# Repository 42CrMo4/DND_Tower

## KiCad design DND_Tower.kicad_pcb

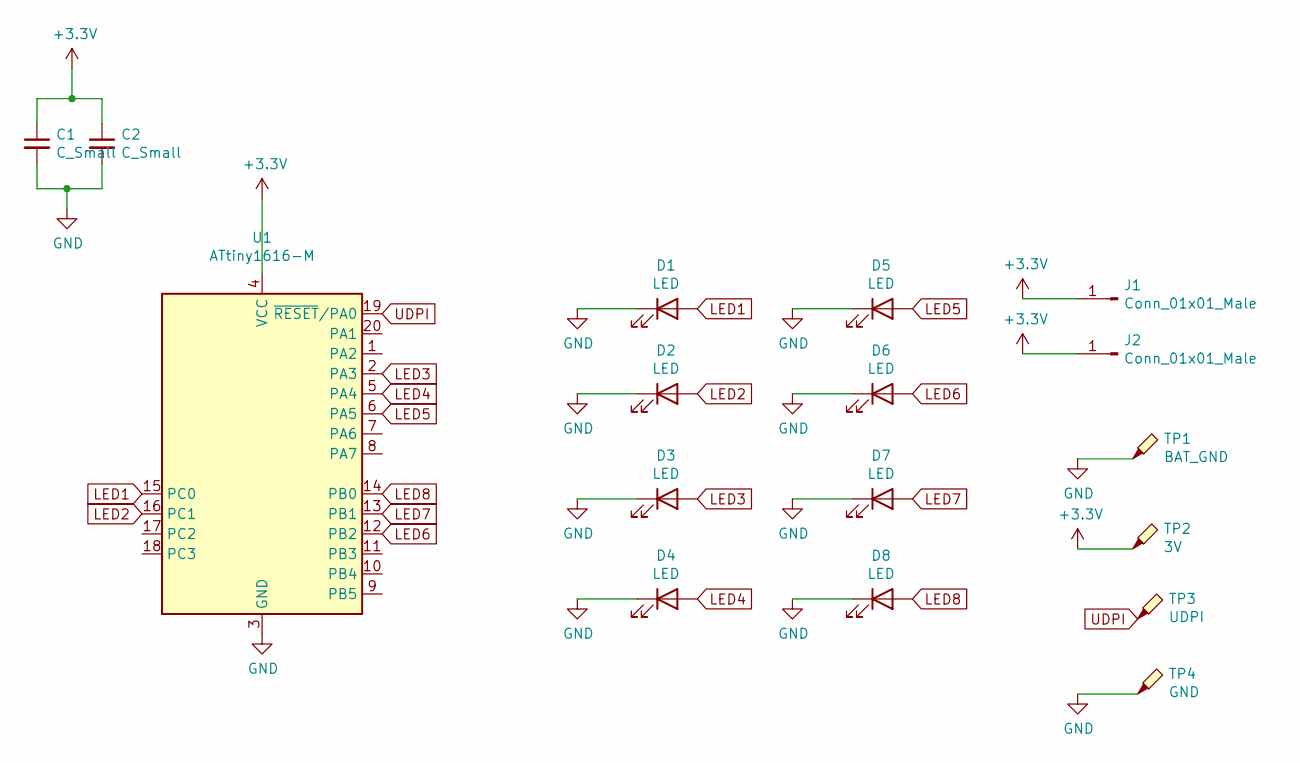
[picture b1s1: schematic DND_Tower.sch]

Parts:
C1, C2: C_Small; C_0805_2012Metric
D1, D2, D3, D4, D5, D6, D7, D8: LED; LED_0805_2012Metric
J1, J2: Conn_01x01_Male; Pin_D1.4mm_L8.5mm_W2.8mm_FlatFork
TP1: BAT_GND; TestPoint_Pad_D4.0mm
TP2: 3V; TestPoint_Pad_D1.0mm
TP3: UDPI; TestPoint_Pad_D1.0mm
TP4: GND; TestPoint_Pad_D1.0mm
U1: ATtiny1616-M; VQFN-20-1EP_3x3mm_P0.4mm_EP1.7x1.7mm

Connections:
+3V3: C1.1, C2.1, J1.1, J2.1, TP2.1, U1.4 (VCC)
GND: C1.2, C2.2, D1.1 (K), D2.1 (K), D3.1 (K), D4.1 (K), D5.1 (K), D6.1 (K), D7.1 (K), D8.1 (K), TP1.1, TP4.1, U1.3 (GND), U1.21 (GND)
LED1: D1.2 (A), U1.15 (PC0)
LED2: D2.2 (A), U1.16 (PC1)
LED3: D3.2 (A), U1.2 (PA3)
LED4: D4.2 (A), U1.5 (PA4)
LED5: D5.2 (A), U1.6 (PA5)
LED6: D6.2 (A), U1.12 (PB2)
LED7: D7.2 (A), U1.13 (PB1)
LED8: D8.2 (A), U1.14 (PB0)
UDPI: TP3.1, U1.19 (~RESET~/PA0)

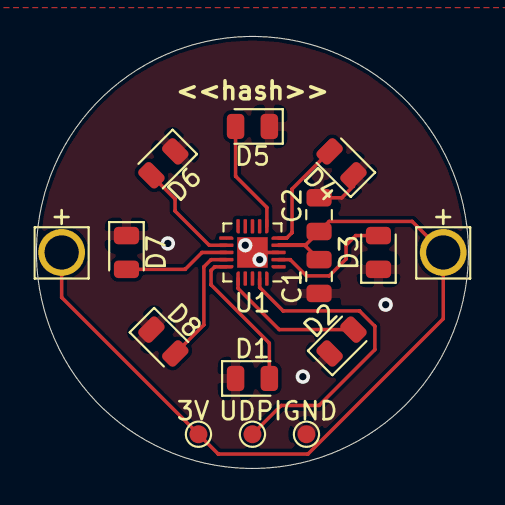
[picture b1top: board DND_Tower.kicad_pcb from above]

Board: 2 copper layers, 24.0 x 24.0 mm, 17 parts (1 on the bottom side), 11 nets.

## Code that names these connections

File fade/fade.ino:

/*
  Fade

  This example shows how to fade an LED on pin 9 using the analogWrite()
  function.

  The analogWrite() function uses PWM, so if you want to change the pin you're
  using, be sure to use another PWM capable pin. On most Arduino, the PWM pins
  are identified with a "~" sign, like ~3, ~5, ~6, ~9, ~10 and ~11.

  This example code is in the public domain.

  https://www.arduino.cc/en/Tutorial/BuiltInExamples/Fade
*/

int led1 = PIN_PC0;           // the PWM pin the LED is attached to
int led2 = PIN_PC1;           // the PWM pin the LED is attached to
int led3 = PIN_PA3;           // the PWM pin the LED is attached to
int led4 = PIN_PA4;           // the PWM pin the LED is attached to
int led5 = PIN_PA5;           // the PWM pin the LED is attached to
int led8 = PIN_PB0;           // the PWM pin the LED is attached to
int led7 = PIN_PB1;           // the PWM pin the LED is attached to
int led6 = PIN_PB2;           // the PWM pin the LED is attached to
int brightness = 0;    // how bright the LED is
int fadeAmount = 5;    // how many points to fade the LED by

// the setup routine runs once when you press reset:
void setup() {
  // declare pin 9 to be an output:
  pinMode(led1, OUTPUT);
  pinMode(led2, OUTPUT);
  pinMode(led3, OUTPUT);
  pinMode(led4, OUTPUT);
  pinMode(led5, OUTPUT);
  pinMode(led6, OUTPUT);
  pinMode(led7, OUTPUT);
  pinMode(led8, OUTPUT);
  digitalWrite(led1, LOW);
  delay(500);
  digitalWrite(led1, HIGH);
}

// the loop routine runs over and over again forever:
void loop() {
  // set the brightness of pin 9:
  analogWrite(led1, brightness - 50);
  analogWrite(led2, 255 - brightness);
  analogWrite(led3, brightness - 50);
  analogWrite(led4, 255 - brightness);
  analogWrite(led5, brightness - 50);
  analogWrite(led6, 255 - brightness);
  analogWrite(led7, brightness - 50);
  analogWrite(led8, 255 - brightness);
  // change the brightness for next time through the loop:
  brightness = brightness + fadeAmount;

  // reverse the direction of the fading at the ends of the fade:
  if (brightness <= 0 || brightness >= 255) {
    fadeAmount = -fadeAmount;
  }
  // wait for 30 milliseconds to see the dimming effect
  delay(30);
}

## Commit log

2021-09-23 init
2021-09-23 yml layout
2021-09-23 name path
2021-09-23 env context
2021-09-23 add kiplot file
2021-09-24 add git hash placeholder
2021-09-24 add pcbdraw font back in
2021-09-24 use png
2021-09-24 add battery holder Datasheet
2021-10-13 add fade arduino program
2021-10-29 add fade circle ino
2021-12-16 3D print cover
